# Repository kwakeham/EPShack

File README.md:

# EPShack
Multiple 3d Printed parts or circuits related to Campagnolo EPS Bike groupset and the micro charger for Campagnolo EPS v2/v3/v4 schematics/pcb (kicad) and the 3d printed enclosures (stl's).

Check out the youtube channel (https://www.youtube.com/channel/UCpfYvYGy5P8HqAfwdeQfTpA) or https://titanlab.co

Video for the hacks is https://youtu.be/waliaKSUcQw

Let me know if you need other stems.

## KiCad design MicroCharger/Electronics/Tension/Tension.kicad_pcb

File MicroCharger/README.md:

#Overview
There are 1 designs here
PCB located in Electronics/Tension
2 Plastic designs are located in Housing MKI-Snap or MKII-Screw

PCB is designed in Kicad, but because of the NTC detection circuit used by the Campagnolo V3/V4 a modification was needed on how to drive the NTC, however this makes the boost voltage important.

Needed
Populated PCB (Tension Board, based on LTC4079 which is an expensive 3x3 10DFN chip)
MT3608 Micro USB boost set to 13.4v.
3D printed housing (MKI or MKII, your preference)
M5 4pin male "sensor cable"

MT3608 Epacket to Canada and this supplier worked well https://www.aliexpress.com/item/MT3608-DC-DC-Adjustable-Boost-Module-2A-Boost-Plate-2A-Step-Up-Module-with-MICRO-USB/32676502704.html?spm=a2g0s.9042311.0.0.6b784c4dcOo234)

M5 Cable https://www.digikey.ca/products/en/cable-assemblies/circular-cable-assemblies/448?k=&pkeyword=&sv=0&pv2344=3&sf=1&FV=24a8000f%2Cffe001c0%2C25300003&quantity=&ColumnSort=0&page=1&stock=1&pageSize=25 (yes, it's expensive!)

So build it then charge your bike, or check out my Tindie store to order one. In action it looks like this

#Build

*NOTE
There is a hack that is necessary. I you want to use this to charge standard 3S lithium it works great, but to use it with a Campagnolo V2/V3/V4 you need to modify the NTC. I'm going to post a new Tension V2 schematic when I update it.*

The LTC pulses the NTC through a completion resistor from the NTC Bias line and reads back the value. The completion resistor is equvalent to the NTC nominal value. However, the EPS unit must read > 0.2v (I think, it's not exactly important) constantly on the NTC to enable charging. This is a charge detection circuit and it triggers the PU to stop functioning while charging as well as acting as a protection.

The LTC4079 wants to see 2v nominally at the NTC. We take away Bias control by NOT populating R5, but instead bias from the main power supply. So we bias the NTC using a 56k resistor to just over 2v from 13.4v. The NTCbias will still pulse but during the read the voltage is supplied elsewhere. The LTC4079 is providing a proper overheat / undertempm safety circuit while tricking the PU into enable charging. Didn't notice this on the original design since I didn't breadboard it. Small mod.

PCB / BOM (html) / etc are located in Electronics

Gerbers in subfolder Gerber. I made mine at PCBway (Rohs copliant, scared of lead) but OSHpark is good. Recommend 0.8mm board instead of 1.6mm to more easily mount LTC4079
Populated it should look like below

Make sure to thread the cable through the hole before soldering first if using MKII screw housing.

M5 4P pinout
Brown - Battery +V
Black - GND / Battery -V
White - NTC (NTC Thermistor other end to GND)
Blue - 12V aux, no longer used in EPS V3/V4

Cable is a 30 dollar CAD norcomp unit, but it's male to male so provides two ends for 2 chargers.

Solder the MT3608 USB boost to the back of the Tension board as shown in the two pictures above. There should be approximately 1mm spacing

#Housing
There are two housings. A snap clost unit and a screw closed.

The snap close snaps from the top but I didn't like the aesthetic finish.

Youtube video shows MKI (snap), photos show MKII (screw). 

Drop PCB in from top, get latches under, press close. Friction Fit

Need to be careful on gap between boards. Slide down, there are grooves to hold them in place so wiggle is the name of the game. Use M3 button head screws on the housing to close through the sides.

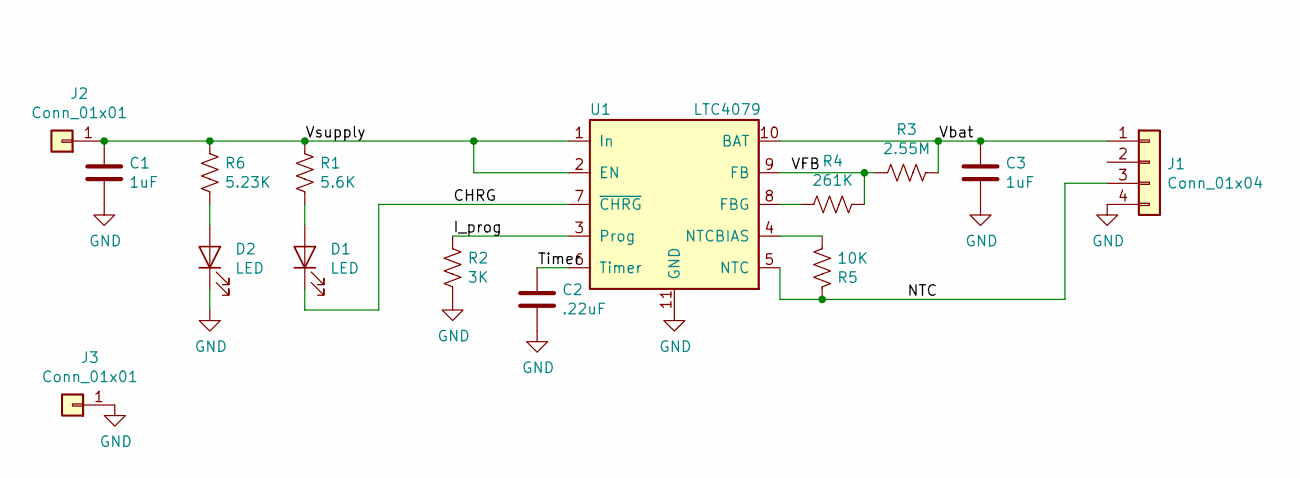
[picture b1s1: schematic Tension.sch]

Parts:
C1, C3: 1uF; C_0805_2012Metric; Digikey 1276-6471-1-ND
C2: .22uF; C_0805_2012Metric; Digikey 311-4267-1-ND
D1: LED; LED_1206_3216Metric; Digikey 754-1940-1-ND
D2: LED; LED_1206_3216Metric; Digikey 754-1943-1-ND
J1: Conn_01x04; SolderWirePad_1x04_P3.81mm_Drill1.2mm
J2, J3: Conn_01x01; SolderWirePad_1x01_Drill1mm
R1: 5.6K; R_0805_2012Metric; Digikey 311-5.6KARCT-ND
R2: 3K; R_0805_2012Metric; Digikey 311-3.00KCRCT-ND
R3: 2.55M; R_0805_2012Metric; Digikey 311-2.55MCRCT-ND
R4: 261K; R_0805_2012Metric; Digikey 311-261KCRCT-ND
R5: 10K; R_0805_2012Metric; Digikey P10KACT-ND
R6: 5.23K; R_0805_2012Metric; Digikey 311-5.23KCRCT-ND
U1: LTC4079; DFN-10-1EP_3x3mm_P0.5mm_EP1.55x2.48mm; Digikey LTC4079EDD#PBF-ND

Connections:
/CHRG: D1.1 (K), U1.7 (~CHRG~)
/I_prog: R2.1, U1.3 (Prog)
/NTC: J1.3, R5.1, U1.5 (NTC)
/Timer: C2.1, U1.6 (Timer)
/VFB: R3.2, R4.1, U1.9 (FB)
/Vbat: C3.1, J1.1, R3.1, U1.10 (BAT)
/Vsupply: C1.1, J2.1, R1.1, R6.1, U1.1 (In), U1.2 (EN)
GND: C1.2, C2.2, C3.2, D2.1 (K), J1.4, J3.1, R2.2, U1.11 (GND)
unnamed: D1.2 (A), R1.2
unnamed: D2.2 (A), R6.2
unnamed: R4.2, U1.8 (FBG)
unnamed: R5.2, U1.4 (NTCBIAS)

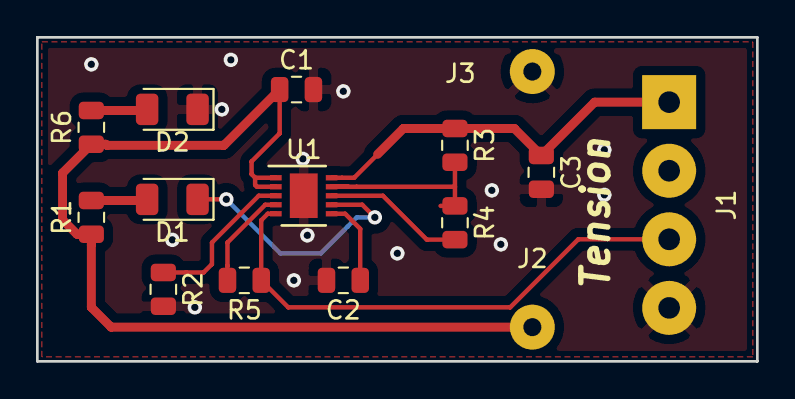
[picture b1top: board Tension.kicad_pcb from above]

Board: 2 copper layers, 40.0 x 18.0 mm, 15 parts (0 on the bottom side), 12 nets.

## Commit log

2019-05-29 Switches
    Added Switches
2019-05-29 Auto stash before merge of "master" and "origin/master"
2019-05-29 Test image in readme.md
    testing what happens to image in readme.me in swtich directory
2019-05-29 fix link to test
2019-05-29 test
2019-05-29 Stem added
2019-05-29 BTL Cage
2019-05-29 Readme.md cage typo
2019-05-29 MicroCharger
2019-05-30 added -12 degree stem
2019-06-04 Wrong cable
    Wrong cable, added digikey seaerch
